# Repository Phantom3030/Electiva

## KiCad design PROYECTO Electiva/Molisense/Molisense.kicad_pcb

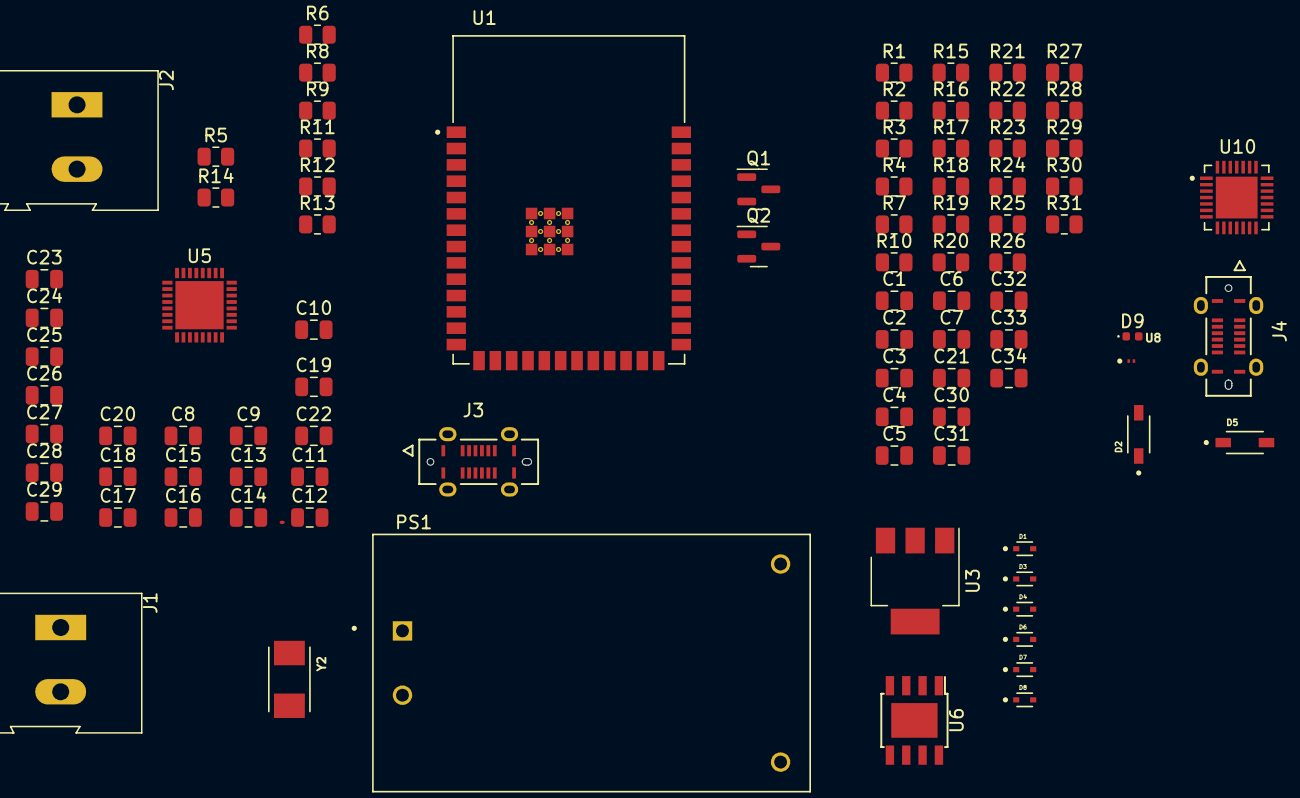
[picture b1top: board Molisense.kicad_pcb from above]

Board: 4 copper layers, 88 parts (0 on the bottom side), 58 nets.

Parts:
C1, C31: 22uF; C_0805_2012Metric
C2, C3, C14, C34: 0.1uF; C_0805_2012Metric
C4, C5, C7, C30, C32: C 10uF; C_0805_2012Metric
C6, C21, C33: 1uF; C_0805_2012Metric
C8, C9: 22Pf; C_0805_2012Metric
C10, C12, C15, C17, C24, C26, C28: 4.7 uF; C_0805_2012Metric
C11, C13, C16, C18, C19, C20, C25, C27, C29: 0.1 uF; C_0805_2012Metric
C22: 15nF; C_0805_2012Metric
C23: 0.47uF; C_0805_2012Metric
D1, D3, D4, D6, D7, D8: LESD5D5.0CT1G; TVS_LESD5D5.0CT1G
D2, D5: 1N5819HW-7-F; SOD3715X145N
D9: LED; LED_0402_1005Metric
J1, J2: Screw_Terminal_01x02; TerminalBlock_Altech_AK300-2_P5.00mm
J3, J4: 2171820001; MOLEX_2171820001
PS1: HLK-PM03; CONV_HLK-PM03
Q1, Q2: NPN; SOT-23
R1, R28: 10K; R_0805_2012Metric
R2, R4, R27: R 10K; R_0805_2012Metric
R3: R 1K; R_0805_2012Metric
R5, R6, R7, R10, R26: 10k; R_0805_2012Metric
R8, R9: 150k; R_0805_2012Metric
R11: 1K; R_0805_2012Metric
R12, R13, R14: 330k; R_0805_2012Metric
R15: R 47K; R_0805_2012Metric
R16, R17, R18, R19, R20, R21, R23, R24, R25, R30: 100k; R_0805_2012Metric
R22: 1k; R_0805_2012Metric
R29: R 22.1K; R_0805_2012Metric
R31: 5.1k; R_0805_2012Metric
U1: ESP32-S3-WROOM-1-N8R8; XCVR_ESP32S3WROOM1N8R8
U3: AMS1117-3.3; SOT-223-3_TabPin2
U5: QFN50P500X500X80-33N
U6: LM358; Diodes_PSOP-8
U8: DIO_PESD5V0R1BSFYL
U10: CP2102N-A02-GQFN28; QFN50P500X500X80-29N
Y2: ABM3-12.000MHZ-D2Y-T; XTAL_ABM3-12.000MHZ-D2Y-T

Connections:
+3.3V: C1.1, C2.1, C5.1, C7.1, C14.1, C15.1, C16.1, C17.1, C18.1, C30.1, C32.1, PS1.4 (+VO), R1.1, R3.1, R5.2, R6.1, R7.1, R28.1, R31.2, U1.2 (3V3), U3.2 (VO), U5.5 (VDD), U5.24 (VDD_2), U6.8 (V+), U8.1, U10.6 (VDD), U10.7 (VREGIN)
+5V: C4.1, D2.C, D5.C, R29.2, U3.3 (VI)
/ADE9153/MIS0: U1.4 (IO4), U5.30 (MISO/TX)
/ADE9153/MISI: U1.38 (IO2), U5.29 (MOSI/RX)
/ADE9153/NEUTRO: J2.2, R14.1, U6.1, U6.2 (-)
/ADE9153/SCLK: U1.22 (IO14), U5.31 (SCLK)
/ADE9153/irq_n: U1.5 (IO5), U5.27 (IRQ_N)
/ADE9153/reset: R6.2, U1.6 (IO6), U5.28 (RESET_N)
/ADE9153/ss: R5.1, U1.8 (IO15), U5.32 (SS_N)
/ESP32-S3-WROOM-1-N8R8/Fases: J2.1, PS1.1 (AC1), R30.1
D+: D4.1, J3.A6 (DP1), U1.19 (IO11)
D+ u: D6.1, J4.A6 (DP1), U10.4 (D+)
D-: D3.2, J3.A7 (DN1), U1.20 (IO12)
D- u: D7.2, J4.A7 (DN1), U10.5 (D-)
DTR: Q2.3 (E), R4.1, U10.28 (DTR)
EN: C3.1, C6.2, Q1.1 (C), R1.2, U1.3 (EN)
GND: C1.2, C2.2, C3.2, C4.2, C5.2, C6.1, C7.2, C8.2, C9.2, C10.2, C11.2, C12.2, C13.2, C14.2, C15.2, C16.2, C17.2, C18.2, C19.1, C20.2, C21.2, C24.1, C25.1, C26.2, C27.2, C28.2, C29.2, C30.2, C31.2, C32.2, C33.1, C34.2, D1.1, D3.1, D4.2, D6.2, D7.1, D8.1, D9.1 (K), J1.2, J3.A1 (GND1), J3.A12 (GND2), J3.B1 (GND3), J3.B12 (GND4), J3.SH1 (SHIELD1), J3.SH2 (SHIELD2), J3.SH3 (SHIELD3), J3.SH4 (SHIELD4), J4.A1 (GND1), J4.A12 (GND2), J4.B1 (GND3), J4.B12 (GND4), J4.SH1 (SHIELD1), J4.SH2 (SHIELD2), J4.SH3 (SHIELD3), J4.SH4 (SHIELD4), PS1.3 (-VO), R2.2, R9.1, R10.2, R15.1, R22.2, U1.1 (GND), U1.40 (GND), U1.41_1 (GND), U1.41_2 (GND), U1.41_3 (GND), U1.41_4 (GND), U1.41_5 (GND), U1.41_6 (GND), U1.41_7 (GND), U1.41_8 (GND), U1.41_9 (GND), U3.1 (GND), U5.1 (DGND), U5.9 (AGND), U5.17 (AGND_2), U5.19 (IBMS), U5.20 (DGND_2), U6.4 (V-), U8.2, U10.3 (GND), U10.29 (GND)
GPIO0: C33.2, C34.1, Q2.1 (C), R28.2, U1.27 (IO0)
unnamed: D9.2 (A), R31.1
unnamed: J1.1, R8.1, U5.6 (IAMS)
unnamed: D1.2, D2.A, J3.A4 (VBUS1), J3.A9 (VBUS2), J3.B4 (VBUS3), J3.B9 (VBUS4)
unnamed: D5.A, D8.2, J4.A4 (VBUS1), J4.A9 (VBUS2), J4.B4 (VBUS3), J4.B9 (VBUS4)
unnamed: Q1.2 (B), R4.2
unnamed: Q2.2 (B), R27.2
unnamed: R12.1, R13.2
unnamed: R13.1, R14.2
unnamed: R16.1, R17.2
unnamed: R17.1, R18.2
unnamed: R18.1, R19.2
unnamed: R19.1, R20.2
unnamed: R20.1, R21.2
unnamed: R21.1, R23.2
unnamed: R23.1, R24.2
unnamed: R24.1, R25.2
unnamed: R25.1, R30.2
unnamed: C24.2, C25.2, U5.16 (AVDDOUT)
unnamed: C8.1, U5.4 (CLKIN), Y2.2
unnamed: C9.1, U5.3 (CLKOUT), Y2.1
unnamed: C10.1, C11.1, U5.2 (DVDDOUT)
unnamed: C23.2, U5.23 (FA0)
unnamed: C23.1, U5.22 (FA1)
unnamed: C19.2, R8.2, U5.7 (IAN)
unnamed: C20.1, R9.2, U5.8 (IAP)
unnamed: U5.11 (IBN), U5.12 (IBP)
unnamed: C28.1, C29.1, U5.21 (MSH)
unnamed: C26.1, C27.1, U5.18 (REFIN)
unnamed: C22.1, R11.1, U5.13 (VAMS), U5.15 (VAN)
unnamed: C22.2, R11.2, R12.2, U5.14 (VAP)
unnamed: C12.1, C13.1, U5.10 (VDDOUT2P5)
unnamed: R7.2, R10.1, U6.3 (+)
unnamed: C31.1, R15.2, R29.1, U10.8 (VBUS)
unnamed: R3.2, U10.9 (~RST)
unnamed: R2.1, U10.11 (~SUSPEND)
RTS: Q1.3 (E), R27.1, U10.24 (RTS)
RX: U1.36 (RXD0), U10.25 (RXD)
TX: U1.37 (TXD0), U10.26 (TXD)
adc: C21.1, R16.2, R22.1, R26.1
adc_in: R26.2, U1.39 (IO1)

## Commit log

2024-02-02 "Finalizado"
2024-04-19 "PCB de pruebas"
